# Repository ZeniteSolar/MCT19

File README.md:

# MCT19
Modulo de controle de temperatura, com modulo wifi

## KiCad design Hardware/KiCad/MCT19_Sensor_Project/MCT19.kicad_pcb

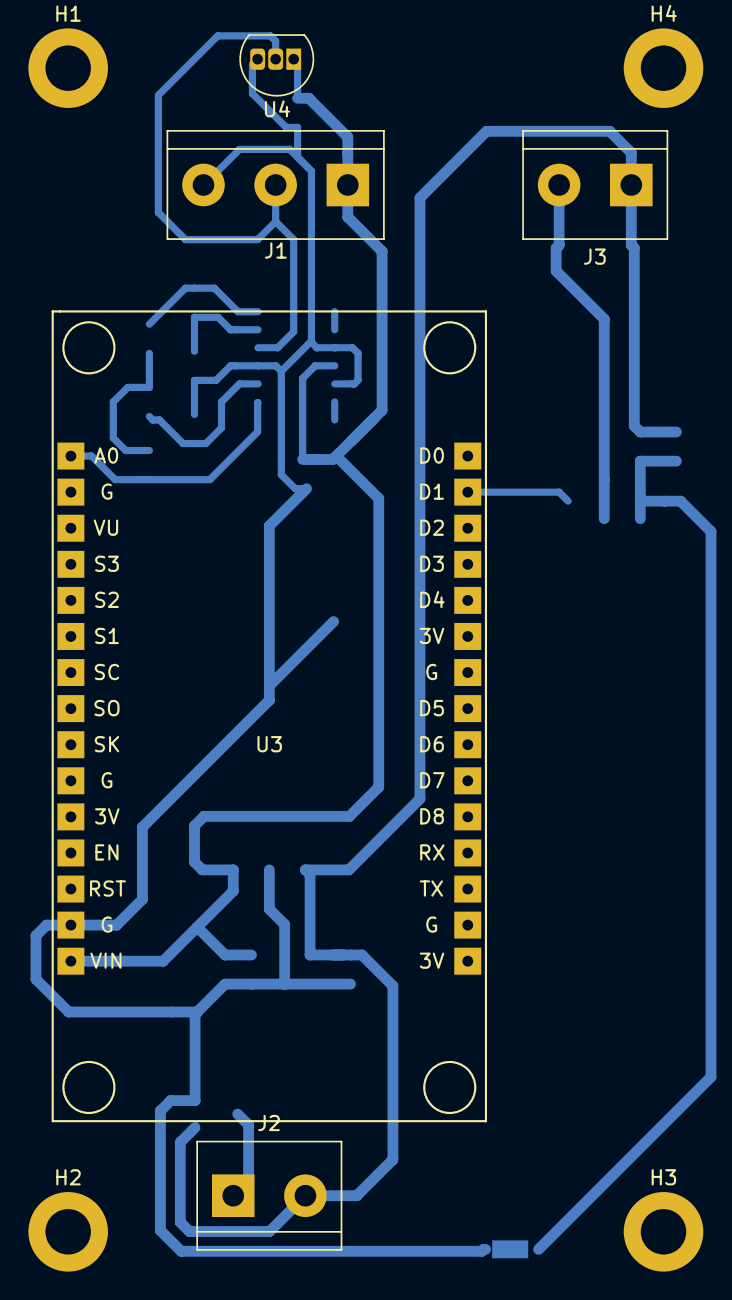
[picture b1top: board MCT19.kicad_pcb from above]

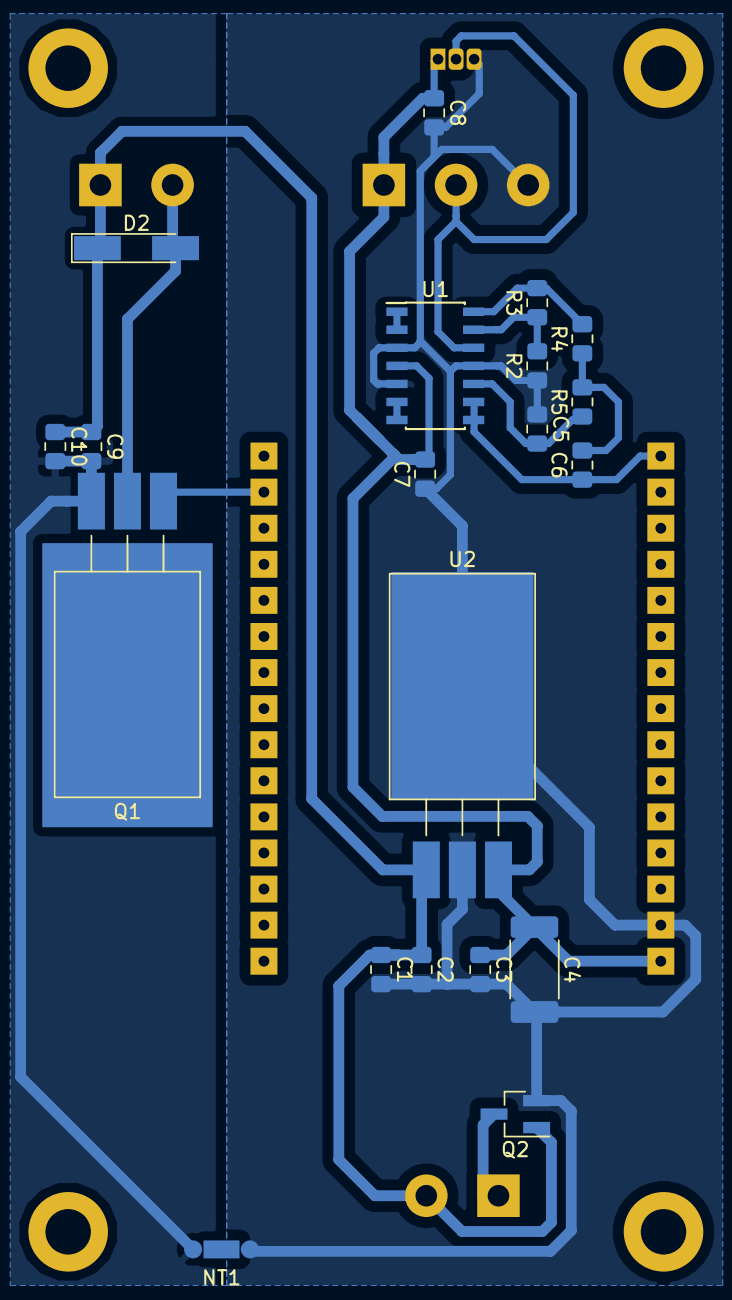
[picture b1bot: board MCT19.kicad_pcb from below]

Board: 2 copper layers, 29 parts (20 on the bottom side), 15 nets.

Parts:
C1, C9, C10: 1u; C_0805_2012Metric_Pad1.15x1.40mm_HandSolder
C2, C3, C7, C8: 100n; C_0805_2012Metric_Pad1.15x1.40mm_HandSolder
C4: 10u; C_2512_6332Metric_Pad1.52x3.35mm_HandSolder
C5, C6: 10n; C_0805_2012Metric_Pad1.15x1.40mm_HandSolder
D2: LL4148; D_MiniMELF_Handsoldering
H1, H2, H3, H4: MountingHole; MountingHole_3.2mm_M3_DIN965_Pad
J1: Sensor; TerminalBlock_bornier-3_P5.08mm
J2: Vin; TerminalBlock_bornier-2_P5.08mm
J3: Fan; TerminalBlock_bornier-2_P5.08mm
NT1: Net-Tie_2; NetTie-2_SMD_Pad_50mil
Q1: Irf530; TO-220-3_Horizontal_TabDown_SMD
Q2: SI2308CDS-T1-GE3; SOT-23_Handsoldering
R2: 50k; R_0805_2012Metric_Pad1.15x1.40mm_HandSolder
R3: 100k; R_0805_2012Metric_Pad1.15x1.40mm_HandSolder
R4, R5: 16k; R_0805_2012Metric_Pad1.15x1.40mm_HandSolder
U1: LM324; SOIC-14_3.9x8.7mm_P1.27mm
U2: L7805; TO-220-3_Horizontal_TabDown_SMD
U3: NodeMCU1.0(ESP-12E); NodeMCU-LoLinV3
U4: LM35-LP; TO-92L_Inline

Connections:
+5V: C3.1, C4.1, C7.2, C8.1, J1.1, U1.4, U2.3, U3.15, U4.1
/Fonte/Vin-: J2.1, Q2.3
/PWM: Q1.1, U3.29
/Sinais/SignalIn: J1.2, U1.12, U4.2
/Sinais/SignalOut: C6.1, U1.8, U1.9, U3.1
GND: C9.2, C10.2, NT1.2, Q1.3
GNDA: C1.2, C2.2, C3.2, C4.2, C5.1, C7.1, C8.2, J1.3, NT1.1, Q2.2, R2.1, U1.3, U1.5, U1.11, U2.2, U2.4, U3.14, U4.3
unnamed: C5.2, R5.1, U1.10
unnamed: C6.2, R4.1, R5.2
unnamed: D2.2, J3.2, Q1.2
unnamed: R2.2, R3.1, U1.13
unnamed: R3.2, R4.2, U1.14
unnamed: U1.1, U1.2
unnamed: U1.6, U1.7
VCC: C1.1, C2.1, C9.1, C10.1, D2.1, J2.2, J3.1, Q2.1, U2.1

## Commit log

2019-01-01 Simulações, Esquemático e Layout placa dos sensores
    *Simulations*:
    -Simulou-se a proteção contra conexão com a polaridade invertida
    -Simulou-se o PWM com um optocoplador (não foi utilizado na versão final)
    -Simulou-se condicionamento de sinais
    *Hardware*
    -Foram utilizadas as bibliotecas do Zênite e foi adicionado uma
2019-01-02 Imagens do 3D e alinhamento
    *hardware*
    -Alinhado no layout os capacitores: C1-C2-C3-C4
    -Adicionaram-se as imagens do 3D em formato png da frente e de tras
